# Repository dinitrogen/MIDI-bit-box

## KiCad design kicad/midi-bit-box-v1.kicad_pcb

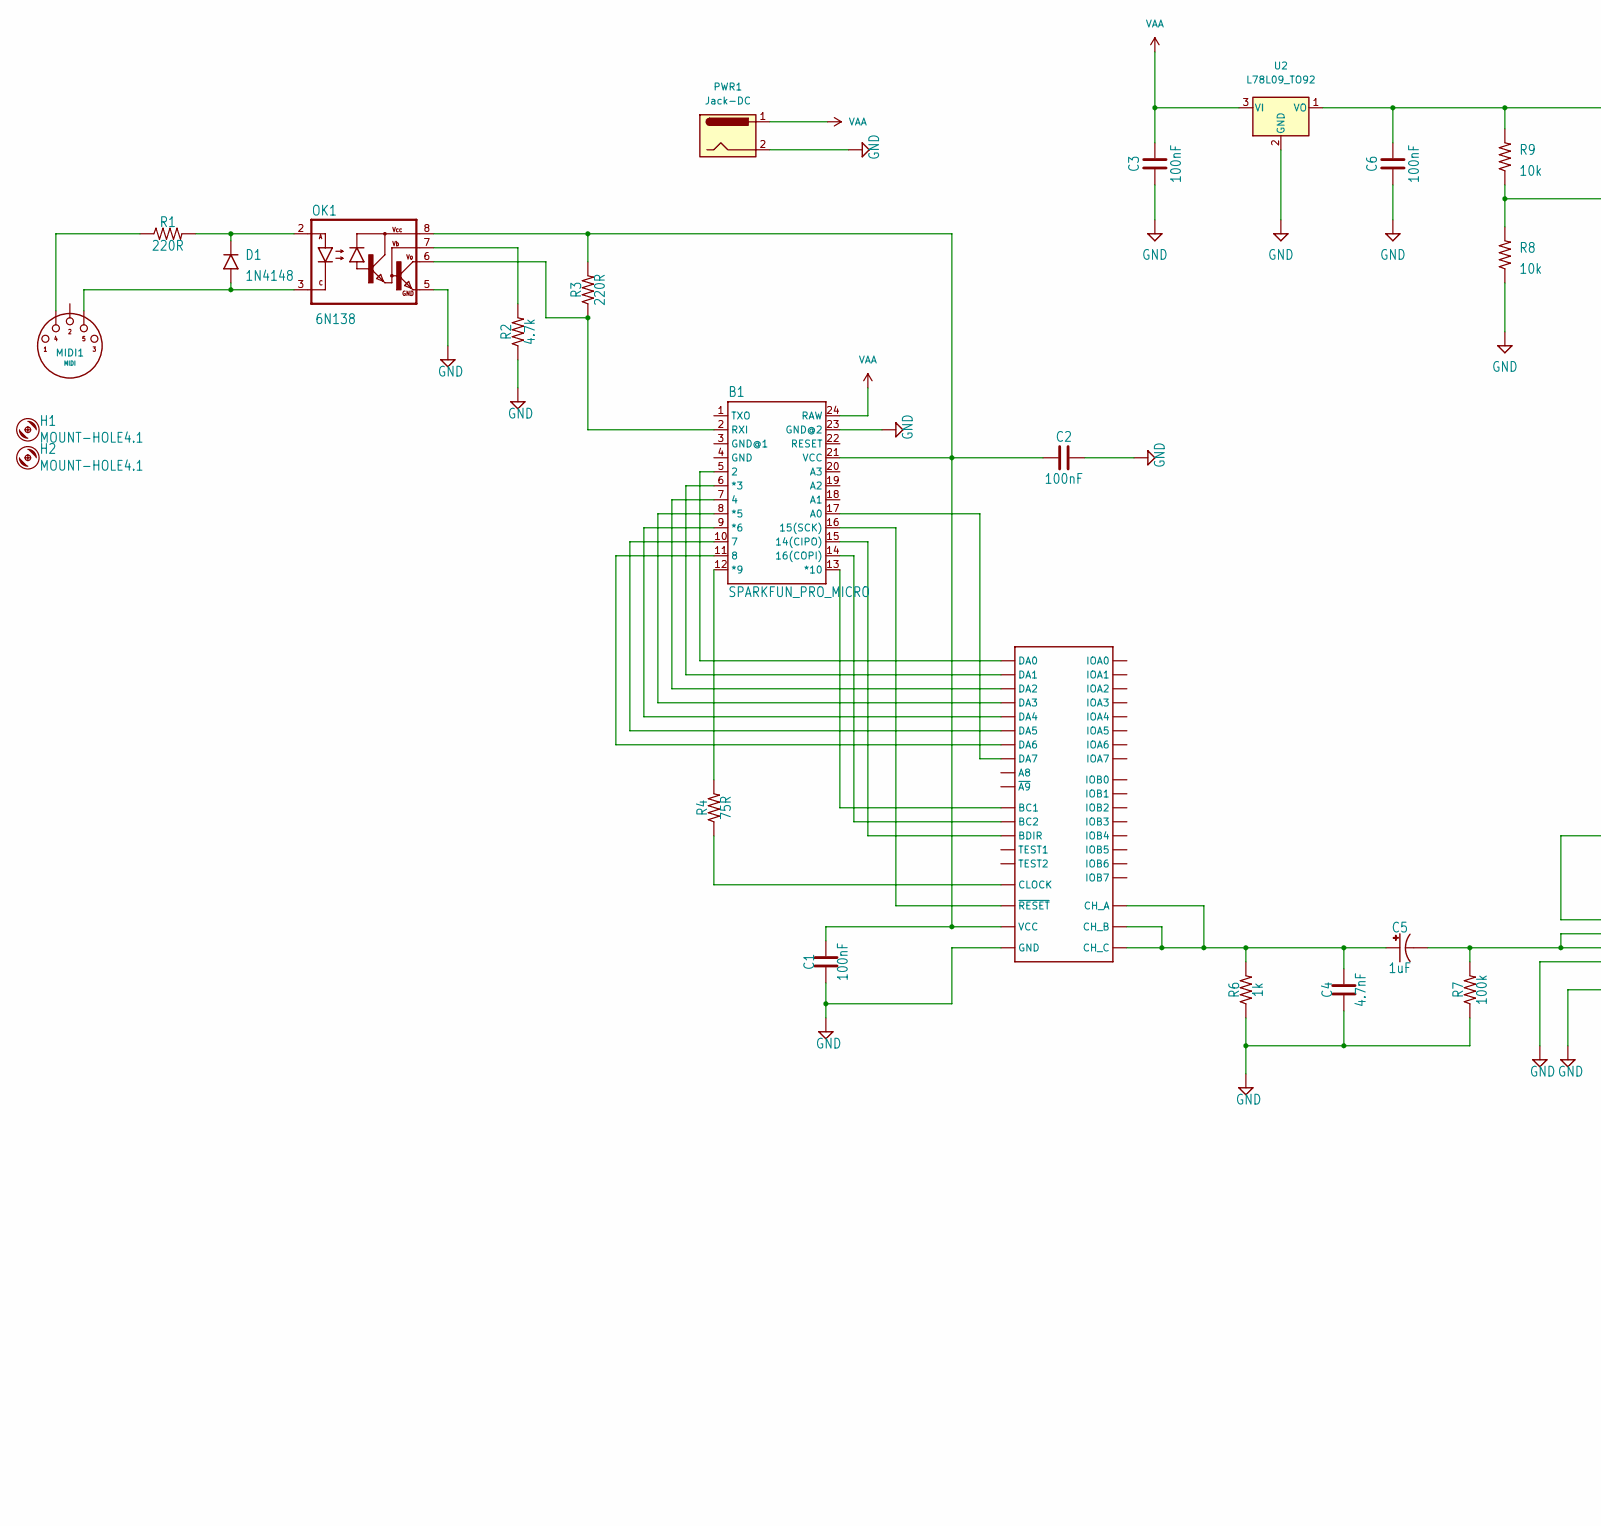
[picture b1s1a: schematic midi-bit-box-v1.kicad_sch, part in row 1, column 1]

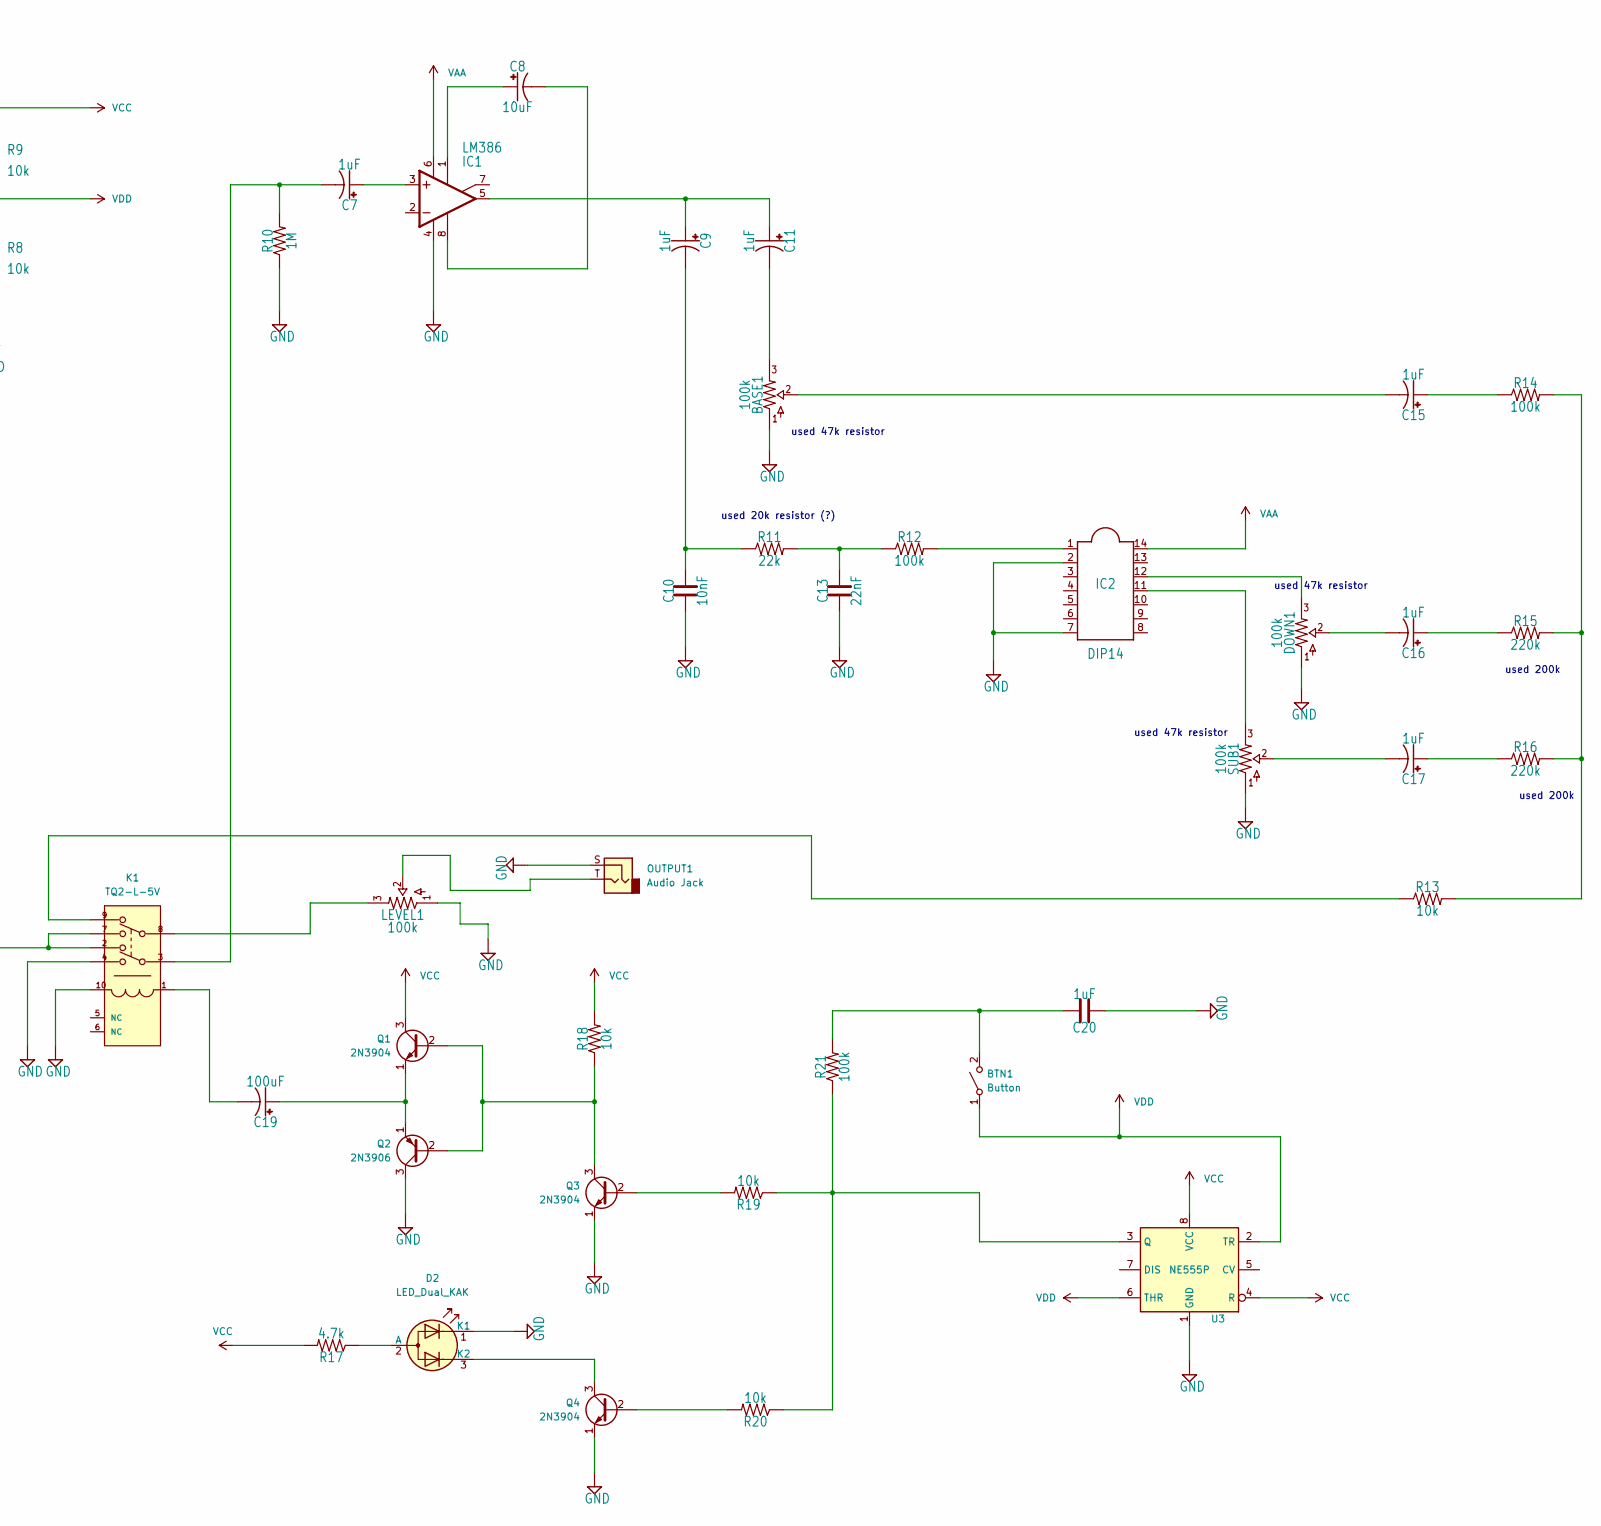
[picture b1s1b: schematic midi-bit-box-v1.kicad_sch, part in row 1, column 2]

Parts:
B1: SPARKFUN_PRO_MICRO
BASE1: 100k; TRIM1
BTN1: Button; ARCADE_BUTTON
C1, C2, C3, C6: 100nF; 0.2_.SML
C4: 4.7nF; 0.2_.SML
C5, C7, C9, C11, C15, C16, C17: 1uF; 0502
C8: 10uF; 0502
C10: 10nF; 0.2_.SML
C13: 22nF; 0.2_.SML
C19: 100uF; 0502
C20: 1uF; 0.2_.SML
D1: 1N4148; DO41-3
D2: LED_Dual_KAK; LED_D5.0mm-3
DOWN1: 100k; TRIM1
H1, H2: MOUNT-HOLE4.1; 4,1
IC1: LM386; DIP08
IC2: DIP14; DIP14.1
K1: TQ2-L-5V; Panasonic-TQ2-L-5V-MFG; coil voltage 5V; current rating 1A; mouser part number 769-TQ2-L-5V; digikey description RELAY TELECOM DPDT 1A 5VDC
LEVEL1: 100k; TRIM1
MIDI1: MIDI; 3PADS
OK1: 6N138; DIP08
OUTPUT1: Audio Jack; 2PADS
PWR1: Jack-DC; DC_TS
Q1, Q3, Q4: 2N3904; TO-92-djk-custom
Q2: 2N3906; TO-92-djk-custom
R1, R3: 220R; 0.3_.B
R2, R17: 4.7k; 0.3_.B
R4: 75R; 0.3_.B
R6: 1k; 0.3_.B
R7, R12, R14, R21: 100k; 0.3_.B
R8, R9, R13, R18, R19, R20: 10k; 0.3_.B
R10: 1M; 0.3_.B
R11: 22k; 0.3_.B
R15, R16: 220k; 0.3_.B
SUB1: 100k; TRIM1
U1: AY-3-8910; DIP-40_600MIL
U2: L78L09_TO92; TO-92-djk-custom
U3: NE555P; DIP-8_W7.62mm

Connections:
GND: B1.23 (GND@2), BASE1.1, C1.2, C2.2, C3.1, C4.1, C6.1, C10.1, C13.1, C20.1, D2.1 (K1), DOWN1.1, IC1.4 (V-), IC2.2, IC2.7, K1.4, K1.10 (S-/R+), LEVEL1.1, OK1.5 (GND), OUTPUT1.S, PWR1.2, Q2.3 (C), Q3.1 (E), Q4.1 (E), R2.1, R6.1, R7.1, R8.1, R10.1, SUB1.1, U1.1 (GND), U2.2 (GND), U3.1 (GND)
unnamed: B1.2 (RXI), OK1.6 (VO), R3.1
unnamed: B1.5 (2), U1.37 (DA0)
unnamed: B1.6 (*3), U1.36 (DA1)
unnamed: B1.7 (4), U1.35 (DA2)
unnamed: B1.8 (*5), U1.34 (DA3)
unnamed: B1.9 (*6), U1.33 (DA4)
unnamed: B1.10 (7), U1.32 (DA5)
unnamed: B1.11 (8), U1.31 (DA6)
unnamed: B1.12 (*9), R4.2
unnamed: B1.13 (*10), U1.29 (BC1)
unnamed: B1.14 (16(COPI)), U1.28 (BC2)
unnamed: B1.15 (14(CIPO)), U1.27 (BDIR)
unnamed: B1.16 (15(SCK)), U1.23 (~RESET)
unnamed: B1.17 (A0), U1.30 (DA7)
unnamed: B1.21 (VCC), C1.1, C2.1, OK1.8 (VCC), R3.2, U1.40 (VCC)
unnamed: BASE1.2, C15.-
unnamed: BASE1.3, C11.-
unnamed: BTN1.2 (B), C20.2, R21.2
unnamed: C4.2, C5.+, R6.2, U1.3 (CH_B), U1.4 (CH_A), U1.38 (CH_C)
unnamed: C5.-, K1.2, K1.7, R7.2
unnamed: C7.+, IC1.3 (+IN)
unnamed: C7.-, K1.3, R10.2
unnamed: C8.+, IC1.1 (GAIN1)
unnamed: C8.-, IC1.8 (GAIN2)
unnamed: C9.-, C10.2, R11.1
unnamed: C9.+, C11.+, IC1.5 (OUT)
unnamed: C13.2, R11.2, R12.1
unnamed: C15.+, R14.1
unnamed: C16.+, R15.1
unnamed: C16.-, DOWN1.2
unnamed: C17.+, R16.1
unnamed: C17.-, SUB1.2
unnamed: C19.+, Q1.1 (E), Q2.1 (E)
unnamed: C19.-, K1.1 (S+/R-)
unnamed: D1.A, MIDI1.S (5), OK1.3 (C)
unnamed: D1.C, OK1.2 (A), R1.2
unnamed: D2.2 (A), R17.1
unnamed: D2.3 (K2), Q4.3 (C)
unnamed: DOWN1.3, IC2.12
unnamed: IC2.1, R12.2
unnamed: IC2.11, SUB1.3
unnamed: K1.8, LEVEL1.3
unnamed: K1.9, R13.1
unnamed: LEVEL1.2, OUTPUT1.T
unnamed: MIDI1.T (4), R1.1
unnamed: OK1.7 (VB), R2.2
unnamed: Q1.2 (B), Q2.2 (B), Q3.3 (C), R18.1
unnamed: Q3.2 (B), R19.2
unnamed: Q4.2 (B), R20.2
unnamed: R4.1, U1.22 (CLOCK)
unnamed: R13.2, R14.2, R15.2, R16.2
unnamed: R19.1, R20.1, R21.1, U3.3 (Q)
VAA: B1.24 (RAW), C3.2, IC1.6 (V+), IC2.14, PWR1.1, U2.3 (VI)
VCC: C6.2, Q1.3 (C), R9.2, R17.2, R18.2, U2.1 (VO), U3.4 (R), U3.8 (VCC)
VDD: BTN1.1 (A), R8.2, R9.1, U3.2 (TR), U3.6 (THR)

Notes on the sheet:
used 20k resistor (?)
used 200k
used 200k
used 47k resistor

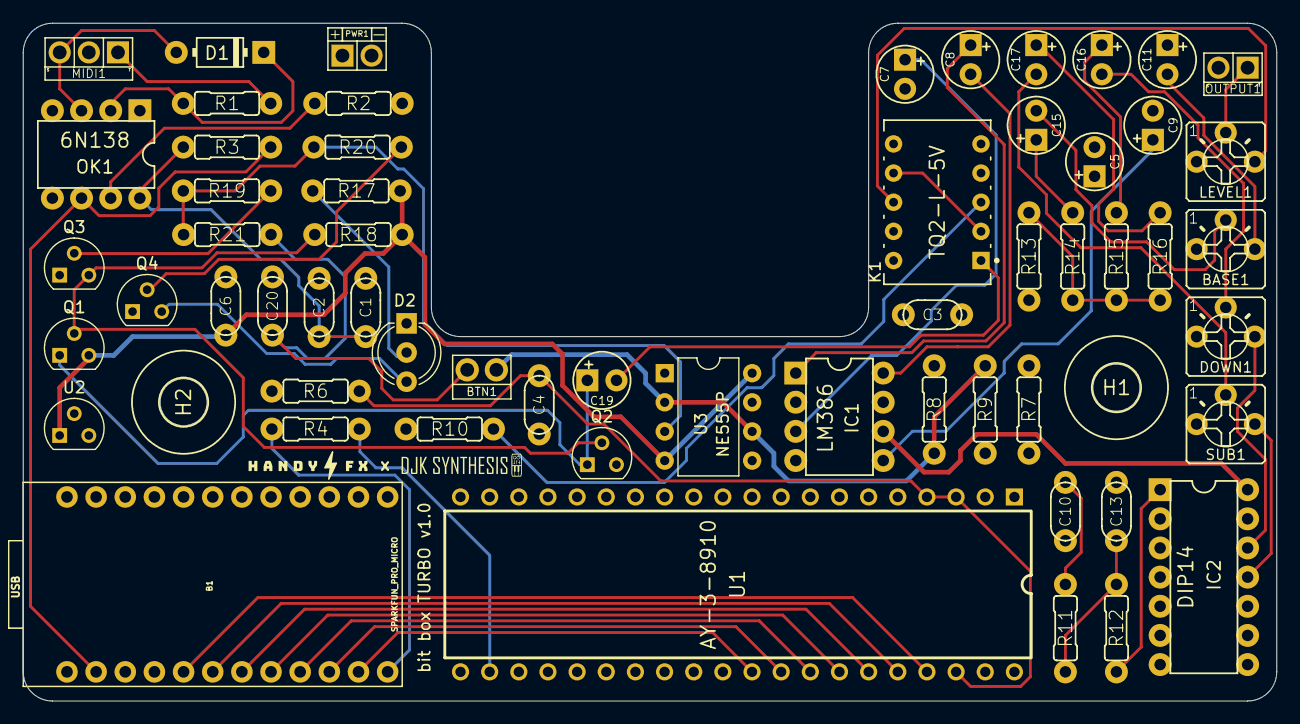
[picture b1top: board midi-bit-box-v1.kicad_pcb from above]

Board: 4 copper layers, 109.2 x 59.1 mm, 61 parts (0 on the bottom side), 56 nets.

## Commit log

2022-01-26 Added SPST and latching relay switching circuit
2022-02-03 Create kicad
2022-02-03 Create deleteme
2022-02-03 Add files via upload
    initial kicad uploads
2022-02-04 Add files via upload
    updated pwr/audio jacks and design rules
2022-02-05 added dual LED
2022-02-07 added trimpot to control output volume
2022-02-08 corrected DC input jack pads
2022-02-08 corrected DC input pad shapes
2022-02-23 enclosure graphic first draft
2022-02-24 added work-in-progress artwork
2022-02-24 updates to enclosure graphic
2022-02-27 draft print files
2022-04-13 Added sketch to test out different DSR envelopes
2022-05-01 Added gerbers
2022-05-01 no startup jingle
